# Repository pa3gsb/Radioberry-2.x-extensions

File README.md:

# Radioberry-2.x-extensions
Hardware extensions to the Radioberry Ham Radio

Deepu Augustin VU3TLD, from India made the next step to make a complete stackable HAM radio.

He started with a Power Amplifier board, based on the G6ALU 20W PA; version 1.5 is available and
the first components are in place.

He also is aiming for a filter board; a version 1.3 is available; first PCB's are underway!

An animation of the idea of such a configuration can be found => Radioberry_radio_assembly.avi file.

Some nice PA details:

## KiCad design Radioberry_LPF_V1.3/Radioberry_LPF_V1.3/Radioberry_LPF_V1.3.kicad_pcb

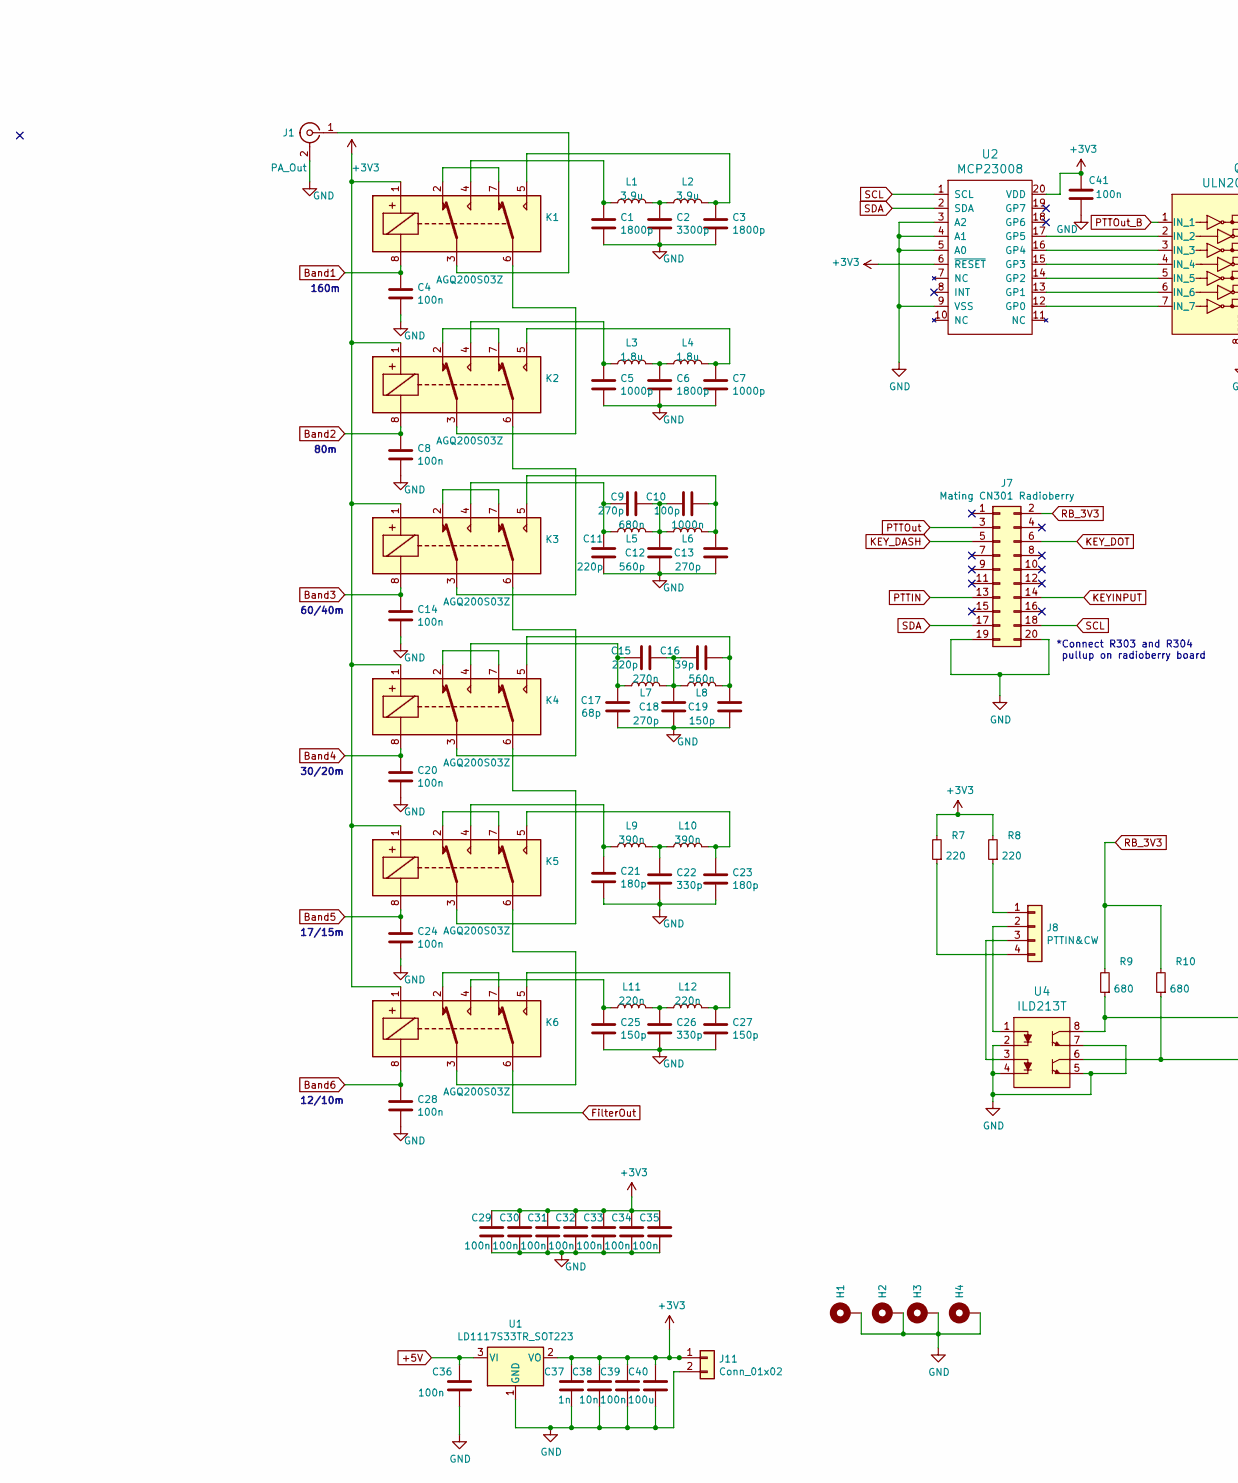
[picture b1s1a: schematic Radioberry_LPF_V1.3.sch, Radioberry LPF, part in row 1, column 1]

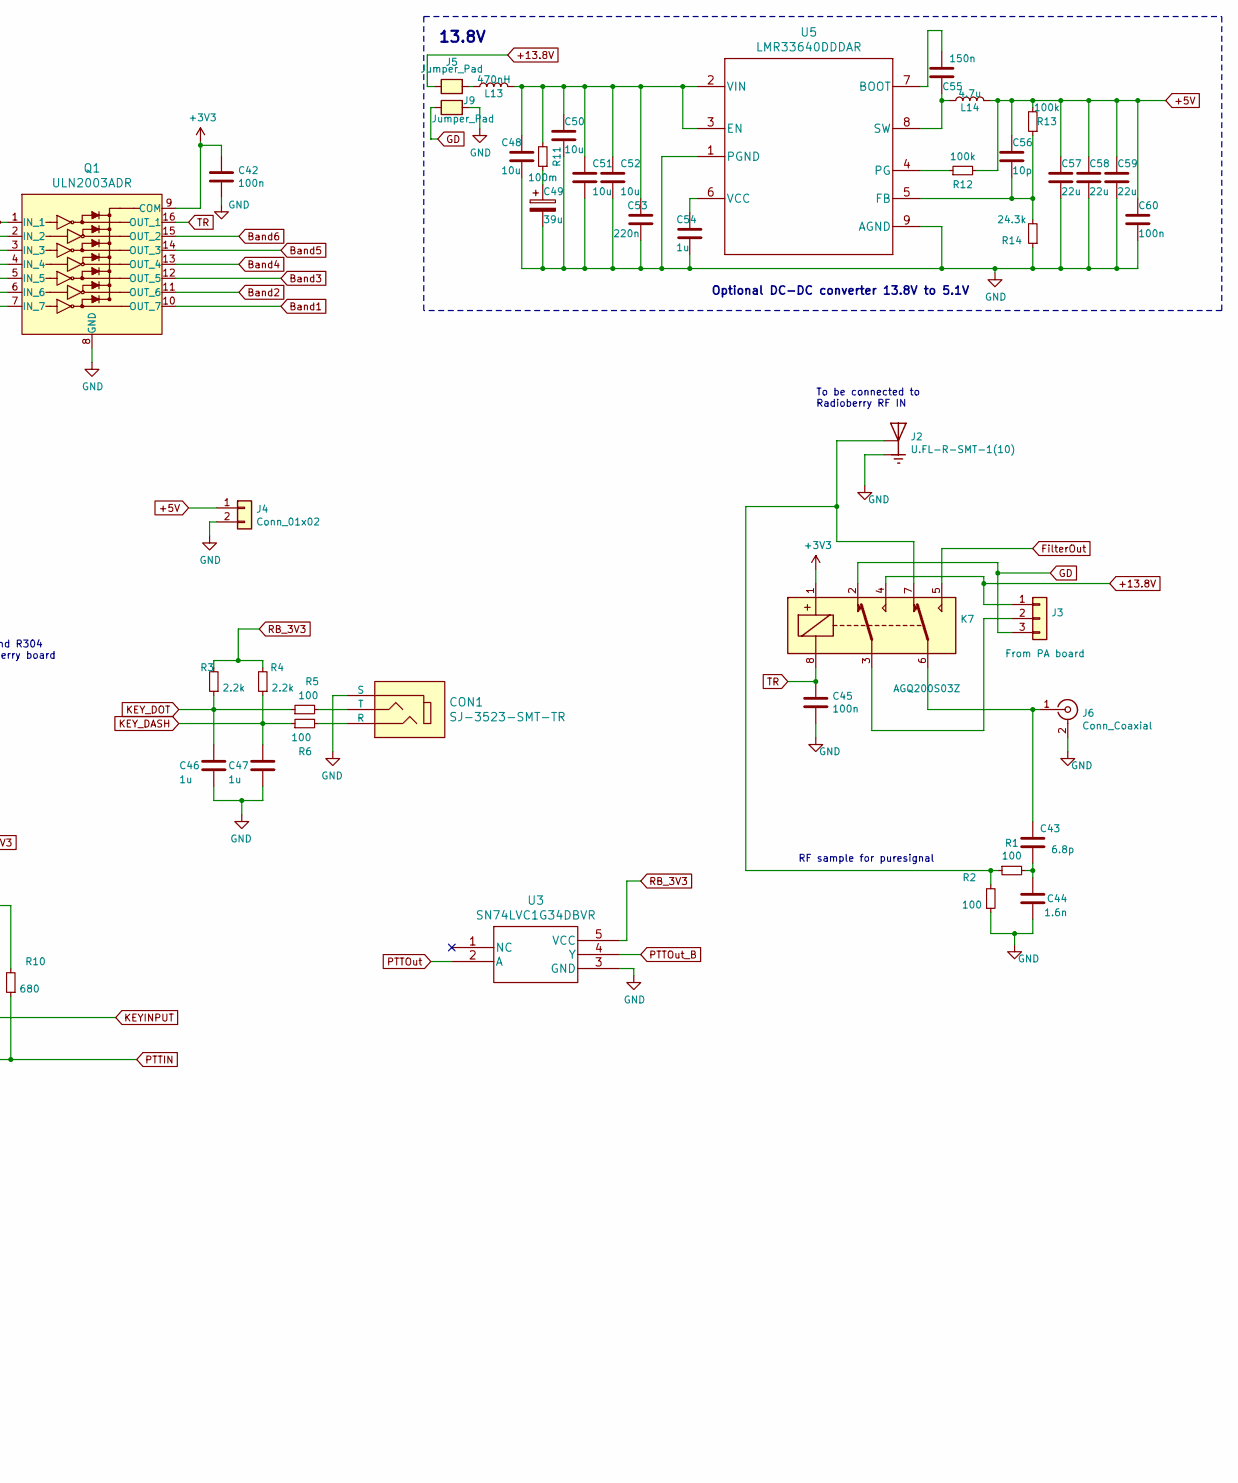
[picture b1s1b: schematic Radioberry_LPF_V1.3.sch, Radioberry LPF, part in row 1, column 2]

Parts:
C1, C3, C6: 1800p; C_0805_2012Metric_Pad1.18x1.45mm_HandSolder; MPN GRM2165C2A182JA01D
C2: 3300p; C_0805_2012Metric_Pad1.18x1.45mm_HandSolder; MPN VJ0805A332JXBTW1BC
C4, C8, C14, C20, C24, C28, C29, C30, C31, C32, C33, C34, C35, C36, C39, C41, C42, C45: 100n; C_0805_2012Metric_Pad1.18x1.45mm_HandSolder; MPN 08055C104KAT2A
C5, C7: 1000p; C_0805_2012Metric_Pad1.18x1.45mm_HandSolder; MPN 885012007088
C9, C13, C18: 270p; C_0805_2012Metric_Pad1.18x1.45mm_HandSolder; MPN CC0805JRNPO0BN271
C10: 100p; C_0805_2012Metric_Pad1.18x1.45mm_HandSolder; MPN 885012007082
C11, C15: 220p; C_0805_2012Metric_Pad1.18x1.45mm_HandSolder; MPN 08051A221JAT2A
C12: 560p; C_0805_2012Metric_Pad1.18x1.45mm_HandSolder; MPN CC0805JRNPO0BN561
C16: 39p; C_0805_2012Metric_Pad1.18x1.45mm_HandSolder; MPN 08051A390JAT2A
C17: 68p; C_0805_2012Metric_Pad1.18x1.45mm_HandSolder; MPN C0805C680J1GACTU
C19, C25, C27: 150p; C_0805_2012Metric_Pad1.18x1.45mm_HandSolder; MPN AC0805JRNPO0BN151
C21, C23: 180p; C_0805_2012Metric_Pad1.18x1.45mm_HandSolder; MPN 08051A181JAT2A
C22, C26: 330p; C_0805_2012Metric_Pad1.18x1.45mm_HandSolder; MPN C0805C331J1GACTU
C37: 1n; C_0805_2012Metric_Pad1.18x1.45mm_HandSolder; MPN 08055C102KAT2A
C38: 10n; C_0805_2012Metric_Pad1.18x1.45mm_HandSolder; MPN 08051C103KAT2A
C40: 100u; C_1206_3216Metric; MPN CL31A107MQHNNWE
C43: 6.8p; C_0805_2012Metric_Pad1.18x1.45mm_HandSolder; MPN AC0805JRNPO0BN151
C44: 1.6n; C_0805_2012Metric_Pad1.18x1.45mm_HandSolder; MPN AC0805JRNPO0BN151
C46, C47: 1u; C_0805_2012Metric_Pad1.18x1.45mm_HandSolder; MPN C0805C105K4RACTU
C48, C50, C51, C52: 10u; C_1206_3216Metric; MPN GRM31CR61E106KA12L
C49: 39u; 16SVPC39MV; MPN 16SVPC39MV
C53: 220n; C_0603_1608Metric_Pad1.08x0.95mm_HandSolder; MPN GRM188R71E224KA88D
C54: 1u; C_0603_1608Metric_Pad1.08x0.95mm_HandSolder; MPN C0603C105Z8VACTU
C55: 150n; C_0603_1608Metric_Pad1.08x0.95mm_HandSolder; MPN GRM188R71A154KA01D
C56: 10p; C_0603_1608Metric_Pad1.08x0.95mm_HandSolder; MPN GRM1885C1H100JA01D
C57, C58, C59: 22u; C_0805_2012Metric; MPN GRM21BR61A226ME44L
C60: 100n; C_0603_1608Metric_Pad1.08x0.95mm_HandSolder; MPN GRM188R71H104KA93D
CON1: SJ-3523-SMT-TR; MPN SJ-3523-SMT-TR; Digi-Key_PN CP-3523SJCT-ND
H1, H2, H3, H4: MountingHole_Pad; MountingHole_2.7mm_Pad
J1: PA_Out; SMA_Amphenol_132291_Vertical
J2: U.FL-R-SMT-1(10); HRS_U.FL-R-SMT-1(10)
J3: From PA board; PinHeader_1x03_P2.54mm_Vertical
J4, J11: Conn_01x02; PinHeader_1x02_P2.54mm_Vertical
J5, J9: Jumper_Pad; Jumper_0805
J6: Conn_Coaxial; SMA_Amphenol_132289_EdgeMount
J7: Mating CN301 Radioberry; PinSocket_2x10_P2.54mm_Vertical
J8: PTTIN&CW; JST_GH_SM04B-GHS-TB_1x04-1MP_P1.25mm_Horizontal
K1, K2, K3, K4, K5, K6, K7: AGQ200S03Z
L1, L2: 3.9u; 744773039; MPN 744773039
L3, L4: 1.8u; 7440450018; MPN 7440450018
L5: 680n; WE-LQS; MPN 744040240068
L6: 1000n; 74406042010; MPN 74406042010
L7: 270n; Taiyo_Yuden_1210; MPN BR L3225TR27M
L8: 560n; 744089430056; MPN 744089430056
L9, L10: 390n; WE-SPC_SMD_4828; MPN 744089420039
L11, L12: 220n; WE-SPC_SMD_4818; MPN 744089410022
L13: 470nH; NLCV32T-R47M-PFR; MPN NLCV32T-R47M-PFR
L14: 4.7u; WE-XHMI_SMD_6060; MPN 74439346047
Q1: ULN2003ADR; SOIC-16_3.9x9.9mm_P1.27mm; MPN ULN2003ADR; Digi-Key_PN 296-1368-1-ND
R1: 100; R_0805_2012Metric
R2, R5, R6: 100; R_0805_2012Metric_Pad1.20x1.40mm_HandSolder
R3, R4: 2.2k; R_0805_2012Metric_Pad1.20x1.40mm_HandSolder
R7, R8: 220; R_0805_2012Metric_Pad1.20x1.40mm_HandSolder
R9, R10: 680; R_0805_2012Metric_Pad1.20x1.40mm_HandSolder
R11: 100m; R_0603_1608Metric_Pad0.98x0.95mm_HandSolder; MPN ERJ-3RSFR10V
R12, R13: 100k; R_0603_1608Metric_Pad0.98x0.95mm_HandSolder; MPN CRCW0603100KFKEA
R14: 24.3k; R_0603_1608Metric_Pad0.98x0.95mm_HandSolder; MPN CRCW060324K3FKEA
U1: LD1117S33TR_SOT223; SOT-223-3_TabPin2
U2: MCP23008; SSOP-20_3.9x8.7mm_P0.635mm; MPN MCP23008-E/P; Digi-Key_PN MCP23008-E/P-ND
U3: SN74LVC1G34DBVR; MPN SN74LVC1G34DBVR
U4: ILD213T; MPN ILD213T
U5: LMR33640DDDAR; MPN LMR33640DDDAR

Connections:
+3V3: C29.1, C30.1, C31.1, C32.1, C33.1, C34.1, C35.1, C37.1, C38.1, C39.1, C40.1, C41.1, C42.1, J11.1, K1.1, K2.1, K3.1, K4.1, K5.1, K6.1, K7.1, Q1.9 (COM), R7.2, R8.2, U1.2 (VO), U2.6 (~RESET), U2.20 (VDD)
+5V: C36.1, C56.1, C57.1, C58.1, C59.1, C60.1, J4.1, L14.2, R12.2, R13.2, U1.3 (VI)
+13.8V: J3.1, J5.2, K7.4
Band1: C4.1, K1.8, Q1.10 (OUT_7)
Band2: C8.1, K2.8, Q1.11 (OUT_6)
Band3: C14.1, K3.8, Q1.12 (OUT_5)
Band4: C20.1, K4.8, Q1.13 (OUT_4)
Band5: C24.1, K5.8, Q1.14 (OUT_3)
Band6: C28.1, K6.8, Q1.15 (OUT_2)
FilterOut: K6.6, K7.5
GD: J3.3, J9.2, K7.2
GND: C1.2, C2.2, C3.2, C4.2, C5.2, C6.2, C7.2, C8.2, C11.2, C12.2, C13.2, C14.2, C17.2, C18.2, C19.2, C20.2, C21.2, C22.2, C23.2, C24.2, C25.2, C26.2, C27.2, C28.2, C29.2, C30.2, C31.2, C32.2, C33.2, C34.2, C35.2, C36.2, C37.2, C38.2, C39.2, C40.2, C41.2, C42.2, C44.2, C45.2, C46.2, C47.2, C48.2, C49.2, C50.2, C51.2, C52.2, C53.2, C54.2, C57.2, C58.2, C59.2, C60.2, CON1.1 (S), H1.1, H2.1, H3.1, H4.1, J1.2 (Ext), J2.1, J2.3, J4.2, J6.2 (Ext), J7.19, J7.20, J9.1, J11.2, Q1.8 (GND), R2.1, R14.1, U1.1 (GND), U2.3 (A2), U2.4 (A1), U2.5 (A0), U2.9 (VSS), U3.3 (GND), U4.2, U4.4, U4.5, U4.7, U5.1 (PGND), U5.9 (AGND)
KEYINPUT: J7.14, R9.1, U4.8
KEY_DASH: C47.1, J7.5, R4.1, R6.1
KEY_DOT: C46.1, J7.6, R3.1, R5.1
unnamed: C1.1, K1.4, L1.1
unnamed: C2.1, L1.2, L2.1
unnamed: C3.1, K1.5, L2.2
unnamed: C5.1, K2.4, L3.1
unnamed: C6.1, L3.2, L4.1
unnamed: C7.1, K2.5, L4.2
unnamed: C9.2, C10.1, C12.1, L5.1, L6.2
unnamed: C10.2, C13.1, K3.5, L6.1
unnamed: C9.1, C11.1, K3.4, L5.2
unnamed: C15.1, C17.1, K4.4, L7.2
unnamed: C15.2, C16.1, C18.1, L7.1, L8.2
unnamed: C16.2, C19.1, K4.5, L8.1
unnamed: C21.1, K5.4, L9.1
unnamed: C22.1, L9.2, L10.1
unnamed: C23.1, K5.5, L10.2
unnamed: C25.1, K6.4, L11.1
unnamed: C26.1, L11.2, L12.1
unnamed: C27.1, K6.5, L12.2
unnamed: C43.1, J6.1 (In), K7.6
unnamed: C43.2, C44.1, R1.2
unnamed: C48.1, C50.1, C51.1, C52.1, C53.1, L13.2, R11.2, U5.2 (VIN), U5.3 (EN)
unnamed: C49.1, R11.1
unnamed: C54.1, U5.6 (VCC)
unnamed: C55.1, U5.7 (BOOT)
unnamed: C55.2, L14.1, U5.8 (SW)
unnamed: C56.2, R13.1, R14.2, U5.5 (FB)
unnamed: CON1.2 (T), R5.2
unnamed: CON1.3 (R), R6.2
unnamed: J1.1 (In), K1.3
unnamed: J2.2, K7.7, R1.1, R2.2
unnamed: J3.2, K7.3
unnamed: J5.1, L13.1
unnamed: J8.1, R8.1
unnamed: J8.2, U4.1
unnamed: J8.3, U4.3
unnamed: J8.4, R7.1
unnamed: K1.2, K1.7
unnamed: K1.6, K2.3
unnamed: K2.2, K2.7
unnamed: K2.6, K3.3
unnamed: K3.2, K3.7
unnamed: K3.6, K4.3
unnamed: K4.2, K4.7
unnamed: K4.6, K5.3
unnamed: K5.2, K5.7
unnamed: K5.6, K6.3
unnamed: K6.2, K6.7
unnamed: Q1.2 (IN_2), U2.17 (GP5)
unnamed: Q1.3 (IN_3), U2.16 (GP4)
unnamed: Q1.4 (IN_4), U2.15 (GP3)
unnamed: Q1.5 (IN_5), U2.14 (GP2)
unnamed: Q1.6 (IN_6), U2.13 (GP1)
unnamed: Q1.7 (IN_7), U2.12 (GP0)
unnamed: R12.1, U5.4 (PG)
PTTIN: J7.13, R10.1, U4.6
PTTOut: J7.3, U3.2 (A)
PTTOut_B: Q1.1 (IN_1), U3.4 (Y)
RB_3V3: J7.2, R3.2, R4.2, R9.2, R10.2, U3.5 (VCC)
SCL: J7.18, U2.1 (SCL)
SDA: J7.17, U2.2 (SDA)
TR: C45.1, K7.8, Q1.16 (OUT_1)

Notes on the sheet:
To be connected to Radioberry RF IN
RF sample for puresignal
Optional DC-DC converter 13.8V to 5.1V
13.8V
*Connect R303 and R304 pullup on radioberry board
12/10m
17/15m
30/20m
60/40m
80m
160m

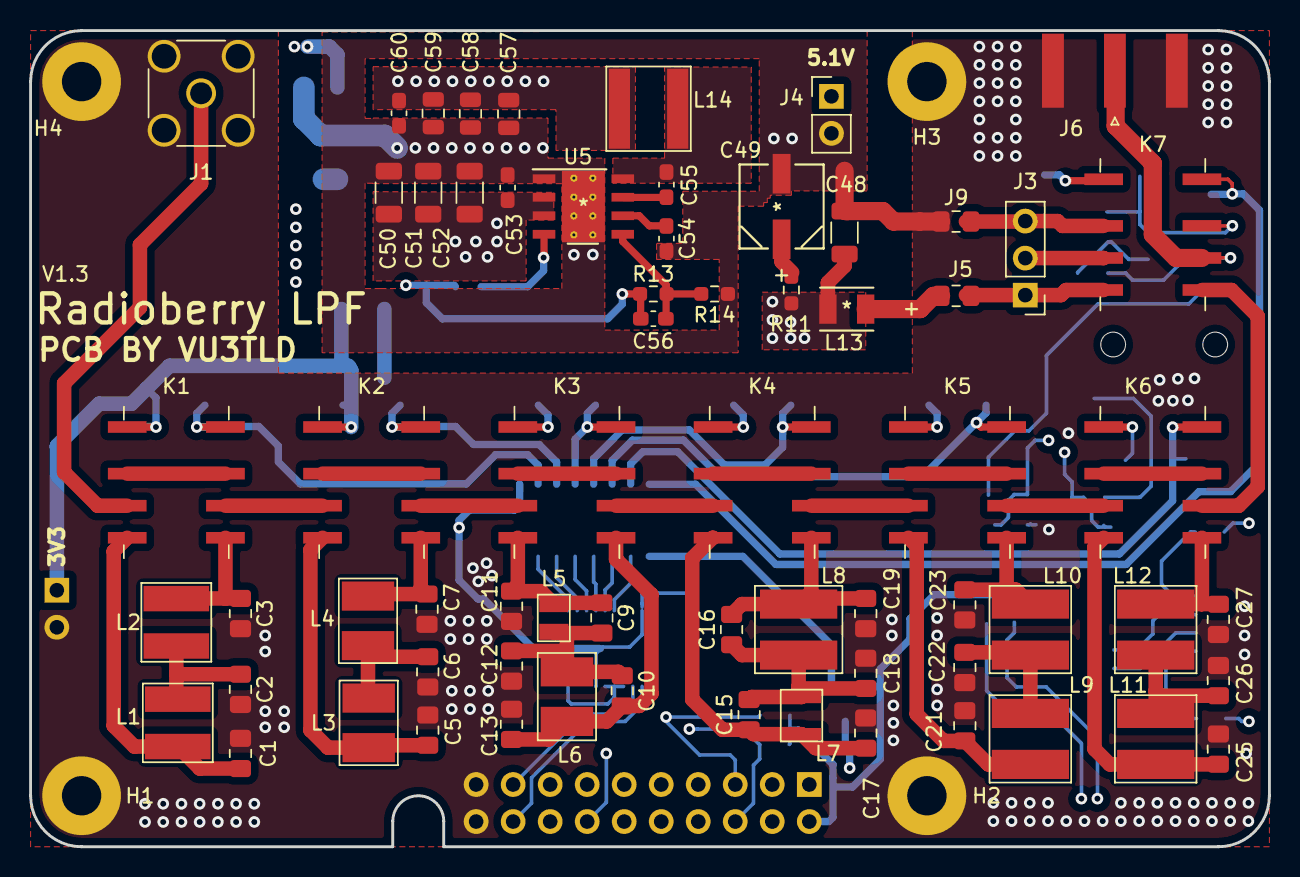
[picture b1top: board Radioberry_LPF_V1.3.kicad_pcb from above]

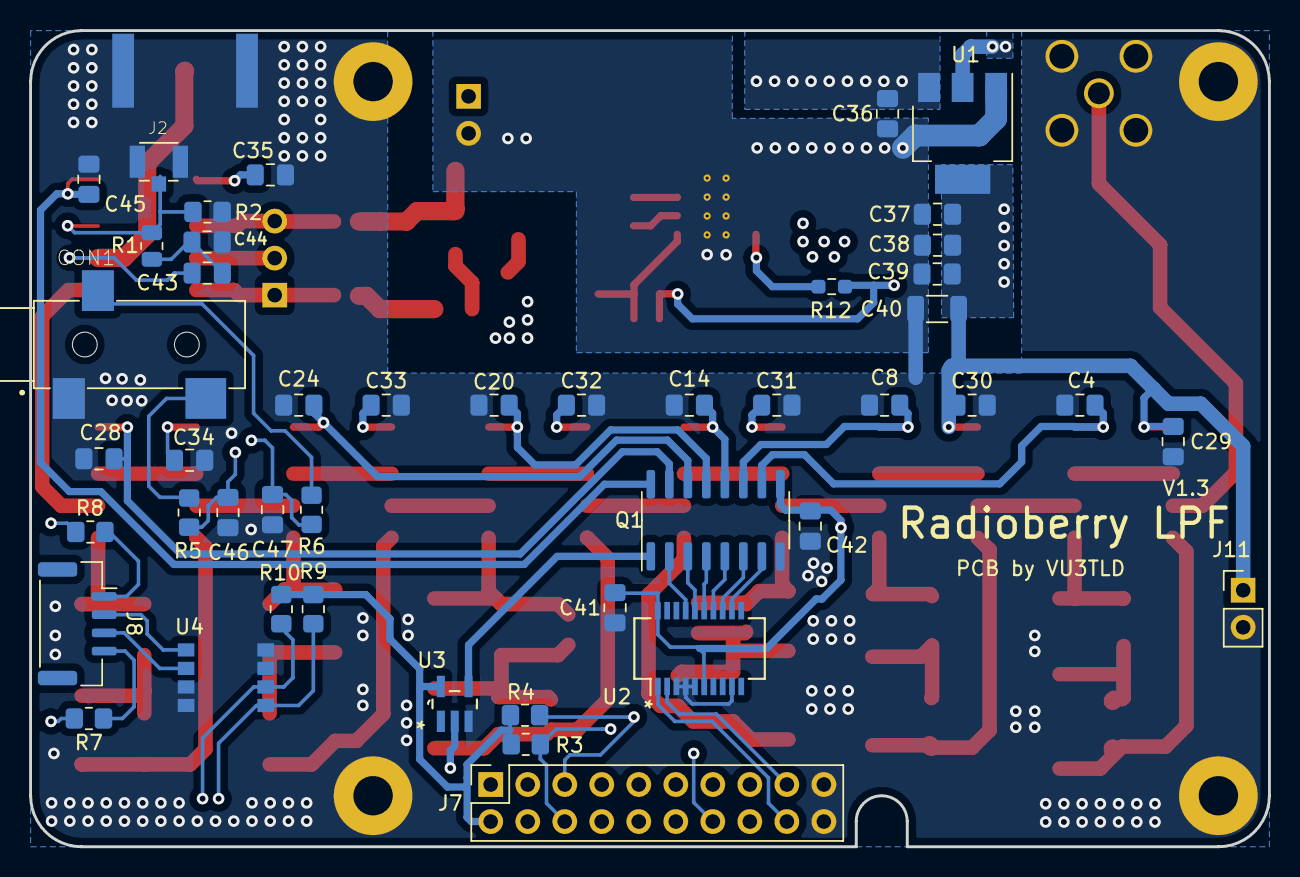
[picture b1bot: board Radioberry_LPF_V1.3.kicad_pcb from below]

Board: 4 copper layers, 85.0 x 56.0 mm, 116 parts (46 on the bottom side), 76 nets.

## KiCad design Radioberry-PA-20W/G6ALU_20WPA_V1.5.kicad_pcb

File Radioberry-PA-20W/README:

As valid for all in the repo all under construction!

Deepu Augustin VU3TLD

Developement of 20W PA for Radioberry.

Based on the work G6ALU_20WPA

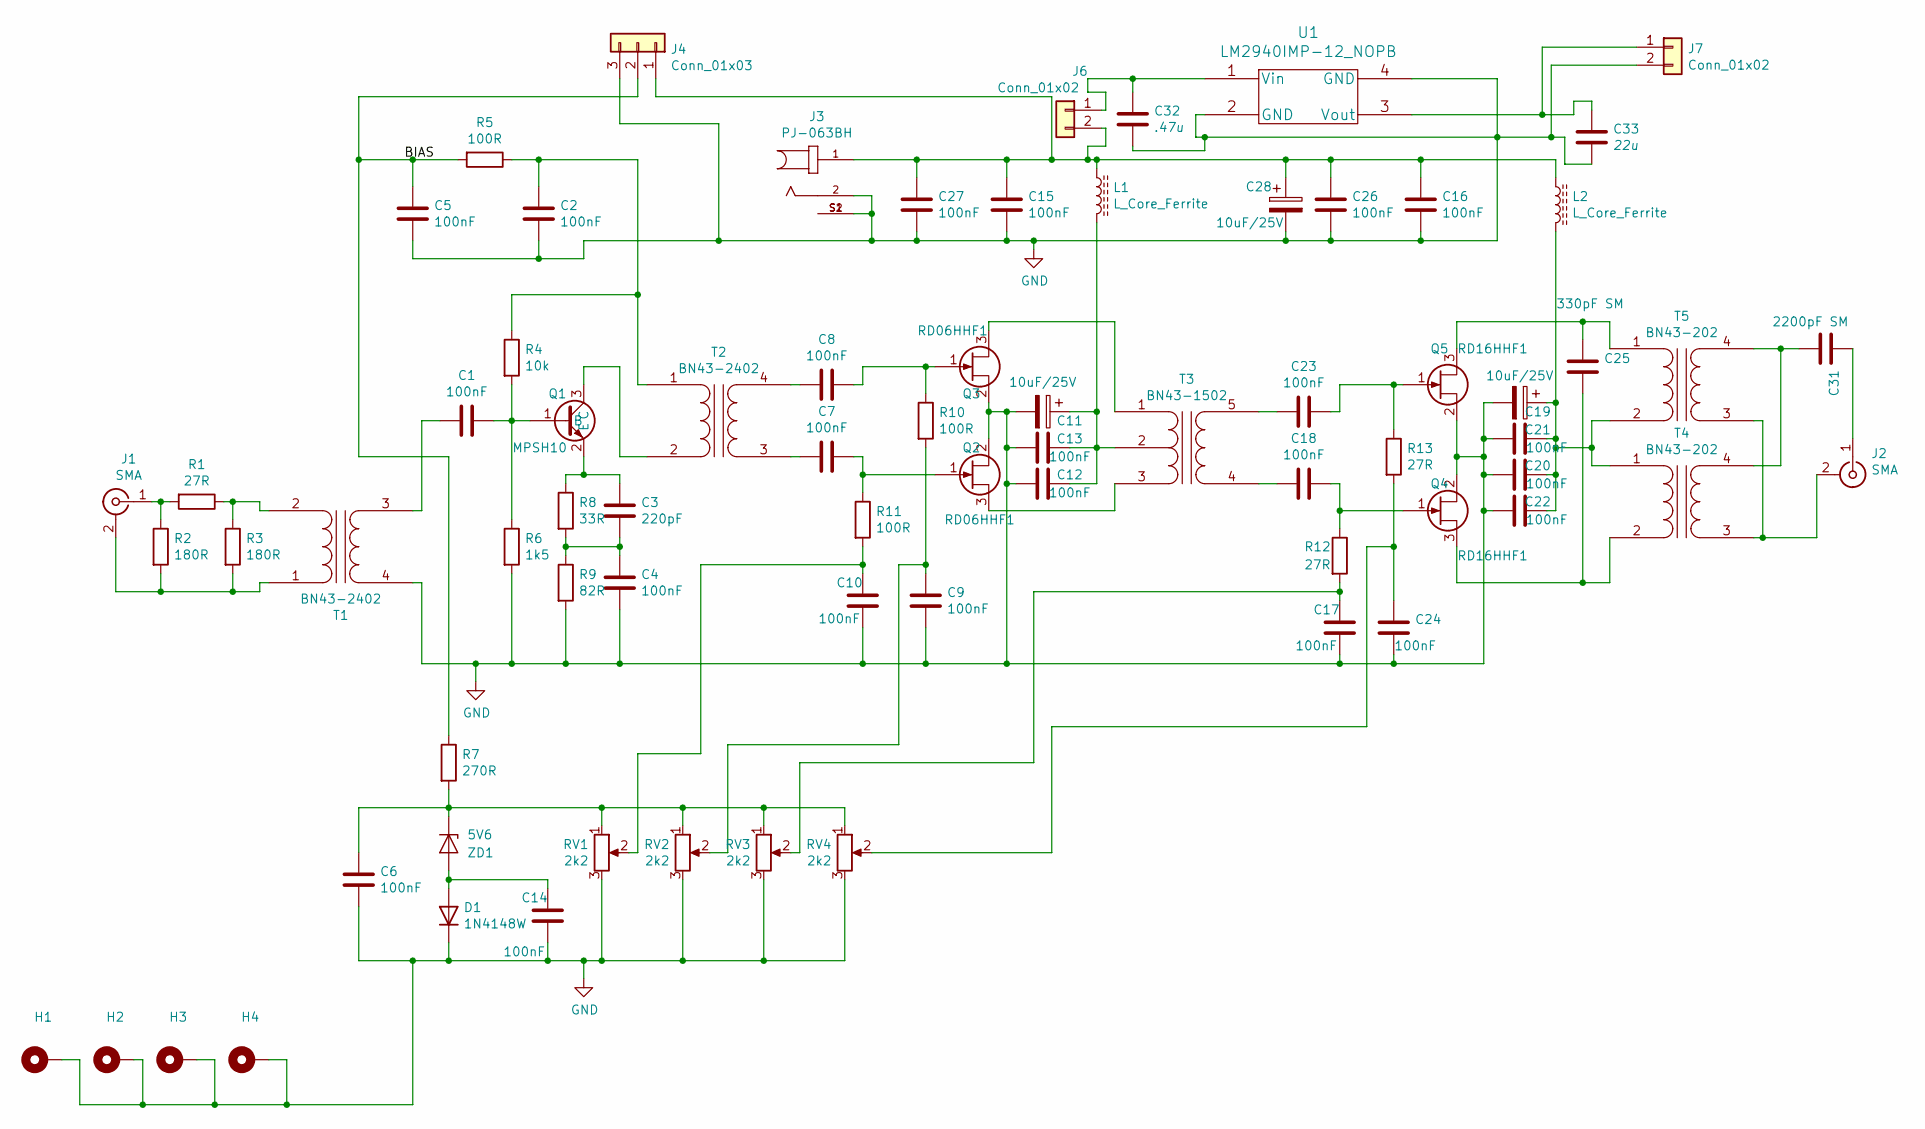
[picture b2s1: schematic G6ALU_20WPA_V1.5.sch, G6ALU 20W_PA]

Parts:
C1, C2, C4, C5, C6, C7, C8, C9, C10, C12, C13, C14, C15, C16, C17, C18, C20, C21, C22, C23, C24, C26, C27: 100nF; C_1206_3216Metric_Pad1.33x1.80mm_HandSolder; Part No. C1206X104K1RAC3316
C3: 220pF; C_1206_3216Metric_Pad1.33x1.80mm_HandSolder; Part No. C1206C221J5GACTU
C11, C19, C28: 10uF/25V; EDK106M025A9BAA; Part No. EDK106M025A9BAA
C25: 330pF SM; CD15FD331JO3; Part No. CD15FD331JO3
C31: 2200pF SM; CD16FD222JO3F; Part No. CD16FD222JO3F
C32: .47u; C_1206_3216Metric_Pad1.33x1.80mm_HandSolder; Part No. CL21B474KBFNNNE
C33: 22u; C_1206_3216Metric_Pad1.33x1.80mm_HandSolder; Part No. CL31A226KAHNNNE
D1: 1N4148W; D_SOD-123; Part No. 1N4148W-E3-08
H1, H2, H3, H4: MountingHole_Pad; MountingHole_2.7mm_Pad_Via
J1, J2: SMA; SMA_RightAngle
J3: PJ-063BH; CUI_PJ-063BH; Part No. PJ-063BH
J4: Conn_01x03; JST_EH_B3B-EH-A_1x03_P2.50mm_Vertical
J6, J7: Conn_01x02; PinHeader_1x02_P2.54mm_Vertical
L1: L_Core_Ferrite; FB_TH_L1; Part No. 901330-01
L2: L_Core_Ferrite; FB_TH_L2; Part No. 901330-01
Q1: MPSH10; TO-92_SMD; Part No. MPSH10
Q2, Q3: RD06HHF1; TO-220_HRZ; Part No. RD06HHF1
Q4, Q5: RD16HHF1; TO-220_HRZ; Part No. RD16HHF1
R1, R12, R13: 27R; R_1206_3216Metric_Pad1.30x1.75mm_HandSolder; Part No. RC1206JR-0727RL
R2, R3: 180R; R_1206_3216Metric_Pad1.30x1.75mm_HandSolder; Part No. RC1206JR-07180RL
R4: 10k; R_1206_3216Metric_Pad1.30x1.75mm_HandSolder; Part No. RC1206JR-0710KL
R5, R10, R11: 100R; R_1206_3216Metric_Pad1.30x1.75mm_HandSolder; Part No. RC1206FR-07100RL
R6: 1k5; R_1206_3216Metric_Pad1.30x1.75mm_HandSolder; Part No. RC1206FR-071K5L
R7: 270R; R_1206_3216Metric_Pad1.30x1.75mm_HandSolder; Part No. ERJ-P08J271V
R8: 33R; R_1206_3216Metric_Pad1.30x1.75mm_HandSolder; Part No. RC1206FR-0733RL
R9: 82R; R_1206_3216Metric_Pad1.30x1.75mm_HandSolder; Part No. RC1206FR-0782RL
RV1, RV2, RV3, RV4: 2k2; POT; Part No. TC33X-1-222E
T1, T2: BN43-2402; Part No. BN43-2402
T3: BN43-1502; Part No. BN43-1502
T4, T5: BN43-202; BN43-202_TH; Part No. BN43-202
U1: LM2940IMP-12_NOPB; LM2940IMP-12&slash_NOPB; Part No. LM2940IMP-12/NOPB
ZD1: 5V6; D_SOD-123; Part No. BZT52C5V6-E3-08

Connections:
/BIAS: C5.2, J4.2, R5.2, R7.1
GND: C2.1, C4.1, C5.1, C6.1, C9.1, C10.1, C11.2, C12.1, C13.1, C14.1, C15.1, C16.1, C17.1, C19.2, C20.2, C21.2, C22.2, C24.1, C26.1, C27.1, C28.2, C32.1, C33.1, D1.1 (K), H1.1, H2.1, H3.1, H4.1, J3.2, J3.S1 (SHIELD), J3.S2 (SHIELD), J4.3, J7.2, Q2.2 (S), Q3.2 (S), Q4.2 (S), Q5.2 (S), R6.2, R9.2, RV1.3, RV2.3, RV3.3, RV4.3, T1.4 (SB), U1.2 (GND), U1.4 (GND)
unnamed: C1.1, Q1.1 (B), R4.2, R6.1
unnamed: C1.2, T1.3 (SA)
unnamed: C2.2, R4.1, R5.1, T2.1 (AA)
unnamed: C3.1, C4.2, R8.2, R9.1
unnamed: C3.2, Q1.2 (E), R8.1
unnamed: C6.2, R7.2, RV1.1, RV2.1, RV3.1, RV4.1, ZD1.1 (K)
unnamed: C7.1, Q2.1 (G), R11.1
unnamed: C7.2, T2.3 (SA)
unnamed: C8.1, Q3.1 (G), R10.1
unnamed: C8.2, T2.4 (SB)
unnamed: C9.2, R10.2, RV2.2
unnamed: C10.2, R11.2, RV1.2
unnamed: C11.1, C12.2, C13.2, L1.2, T3.2 (PM)
unnamed: C14.2, D1.2 (A), ZD1.2 (A)
unnamed: C15.2, C16.2, C26.2, C27.2, C28.1, J3.1, J4.1, J6.2, L1.1, L2.1
unnamed: C17.2, R12.2, RV3.2
unnamed: C18.1, Q4.1 (G), R12.1
unnamed: C18.2, T3.4 (S1)
unnamed: C19.1, C20.1, C21.1, C22.1, L2.2, T4.1 (AA), T5.2 (AB)
unnamed: C23.1, Q5.1 (G), R13.1
unnamed: C23.2, T3.5 (S2)
unnamed: C24.2, R13.2, RV4.2
unnamed: C25.1, Q4.3 (D), T4.2 (AB)
unnamed: C25.2, Q5.3 (D), T5.1 (AA)
unnamed: C31.1, T4.4 (SB), T5.4 (SB)
unnamed: C31.2, J2.1 (In)
unnamed: C32.2, J6.1, U1.1 (Vin)
unnamed: C33.2, J7.1, U1.3 (Vout)
unnamed: J1.1 (In), R1.2, R2.1
unnamed: J1.2 (Ext), R2.2, R3.2, T1.1 (AA)
unnamed: J2.2 (Ext), T4.3 (SA), T5.3 (SA)
unnamed: Q1.3 (C), T2.2 (AB)
unnamed: Q2.3 (D), T3.3 (PR2)
unnamed: Q3.3 (D), T3.1 (PR1)
unnamed: R1.1, R3.1, T1.2 (AB)

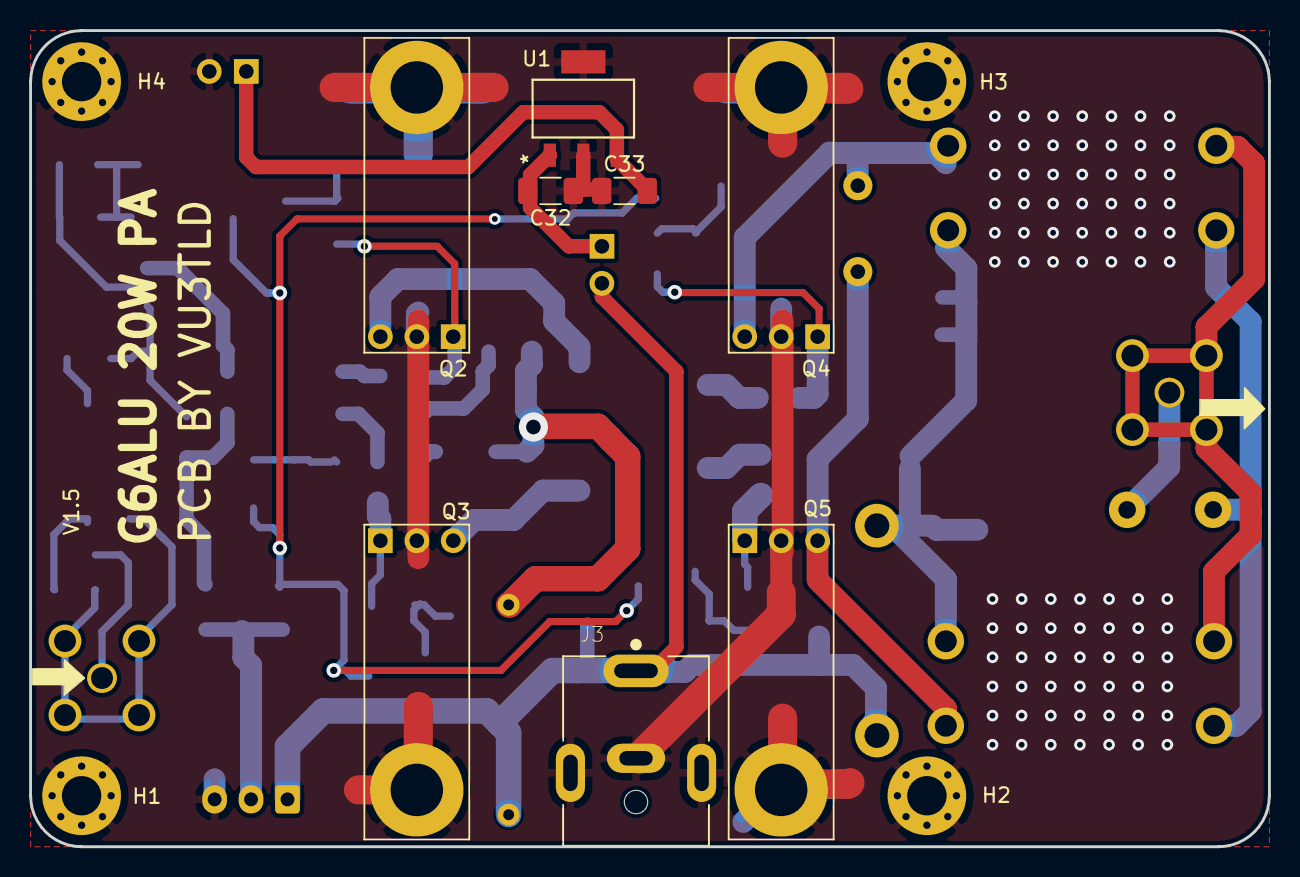
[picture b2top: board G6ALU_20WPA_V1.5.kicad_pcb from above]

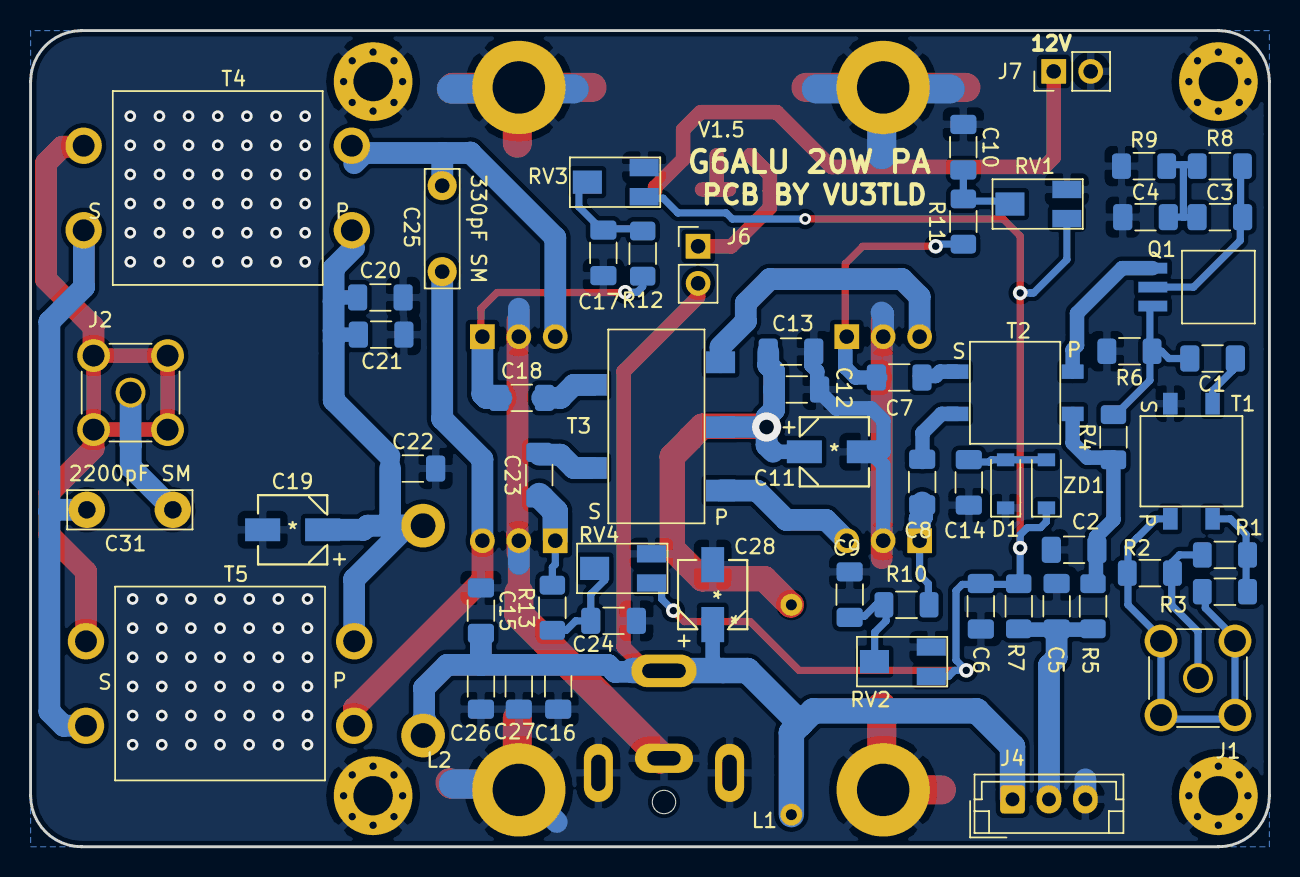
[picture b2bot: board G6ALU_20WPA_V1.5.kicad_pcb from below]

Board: 2 copper layers, 85.0 x 56.0 mm, 73 parts (61 on the bottom side), 37 nets.

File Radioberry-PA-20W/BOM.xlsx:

Id | Designator | Package | Quantity | Designation | Supplier and ref
1 | R10,R5,Re | R_1206_3216Metric | 3 | 100
2 | K1 | G6K-2F-Y | 1 | G6K-2F-Y-DC5
3 | J5,J3,J4 | PinHeader_1x02_P2.54mm_Vertical | 3 | Conn_01x02
4 | J1 | U.FL_Hirose_U.FL-R-SMT-1_Vertical | 1 | UFL-Male
5 | D1 | D_SOD-323 | 1 | PDZ5.6B
6 | C1,C2,C4,C5,C6,C7,C8,C9,C10,C12,C13,C14,C15,C16,C17,C18,C20,C21,C22,C23,C24,C26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 | C_1206_3216Metric | 23 | 100nF
7 | C3 | C_1206_3216Metric | 1 | 220pF
8 | C11,C19,C28 | CP_SMD | 3 | 10uF
9 | C25 | C_SM | 1 | 330pF SM
10 | C31 SM | C_SM | 1 | 2200pF SM
11 | D2 | D_SOD-123 | 1 | 1N4148W
12 | J2 | SMA_Amphenol_901-144_Vertical | 1 | Conn_Coaxial
13 | L1,L2 | FB_SMD | 2 | L_Core_Ferrite
14 | Q1 | TO-92_SMD | 1 | MPSH10
15 | Q2,Q3 | TO-220_HRZ | 2 | RD06HHF1
16 | Q4,Q5 | TO-220_HRZ | 2 | RD16HHF1
17 | R1,R12,R13 | R_1206_3216Metric | 3 | 27
18 | R2,R3 | R_1206_3216Metric | 2 | 180
19 | R4 | R_1206_3216Metric | 1 | 10k
20 | R6 | R_1206_3216Metric | 1 | 1k5
21 | R7 | R_1206_3216Metric | 1 | 270
22 | R8 | R_1206_3216Metric | 1 | 33
23 | R9 | R_1206_3216Metric | 1 | 82
24 | RV1,RV2,RV3,RV4 | POT | 4 | 2k2
25 | T1,T2 | BN43-2402 | 2 | BN43-2402
26 | T3 | BN43-1502 | 1 | BN43-1502
27 | T4,T5 | BN43-202 | 2 | BN43-202

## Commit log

2020-04-24 project init
2020-04-24 readme
2020-11-24 1.5 PA and 1.3 filter

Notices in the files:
parts and their libraries:
Copyright 2016 Accelerated Designs. All rights reserved.
